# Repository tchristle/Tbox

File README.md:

# Tbox
Teensy3, esp8266, HC05, ssd1306, imu, and GPS in a kit

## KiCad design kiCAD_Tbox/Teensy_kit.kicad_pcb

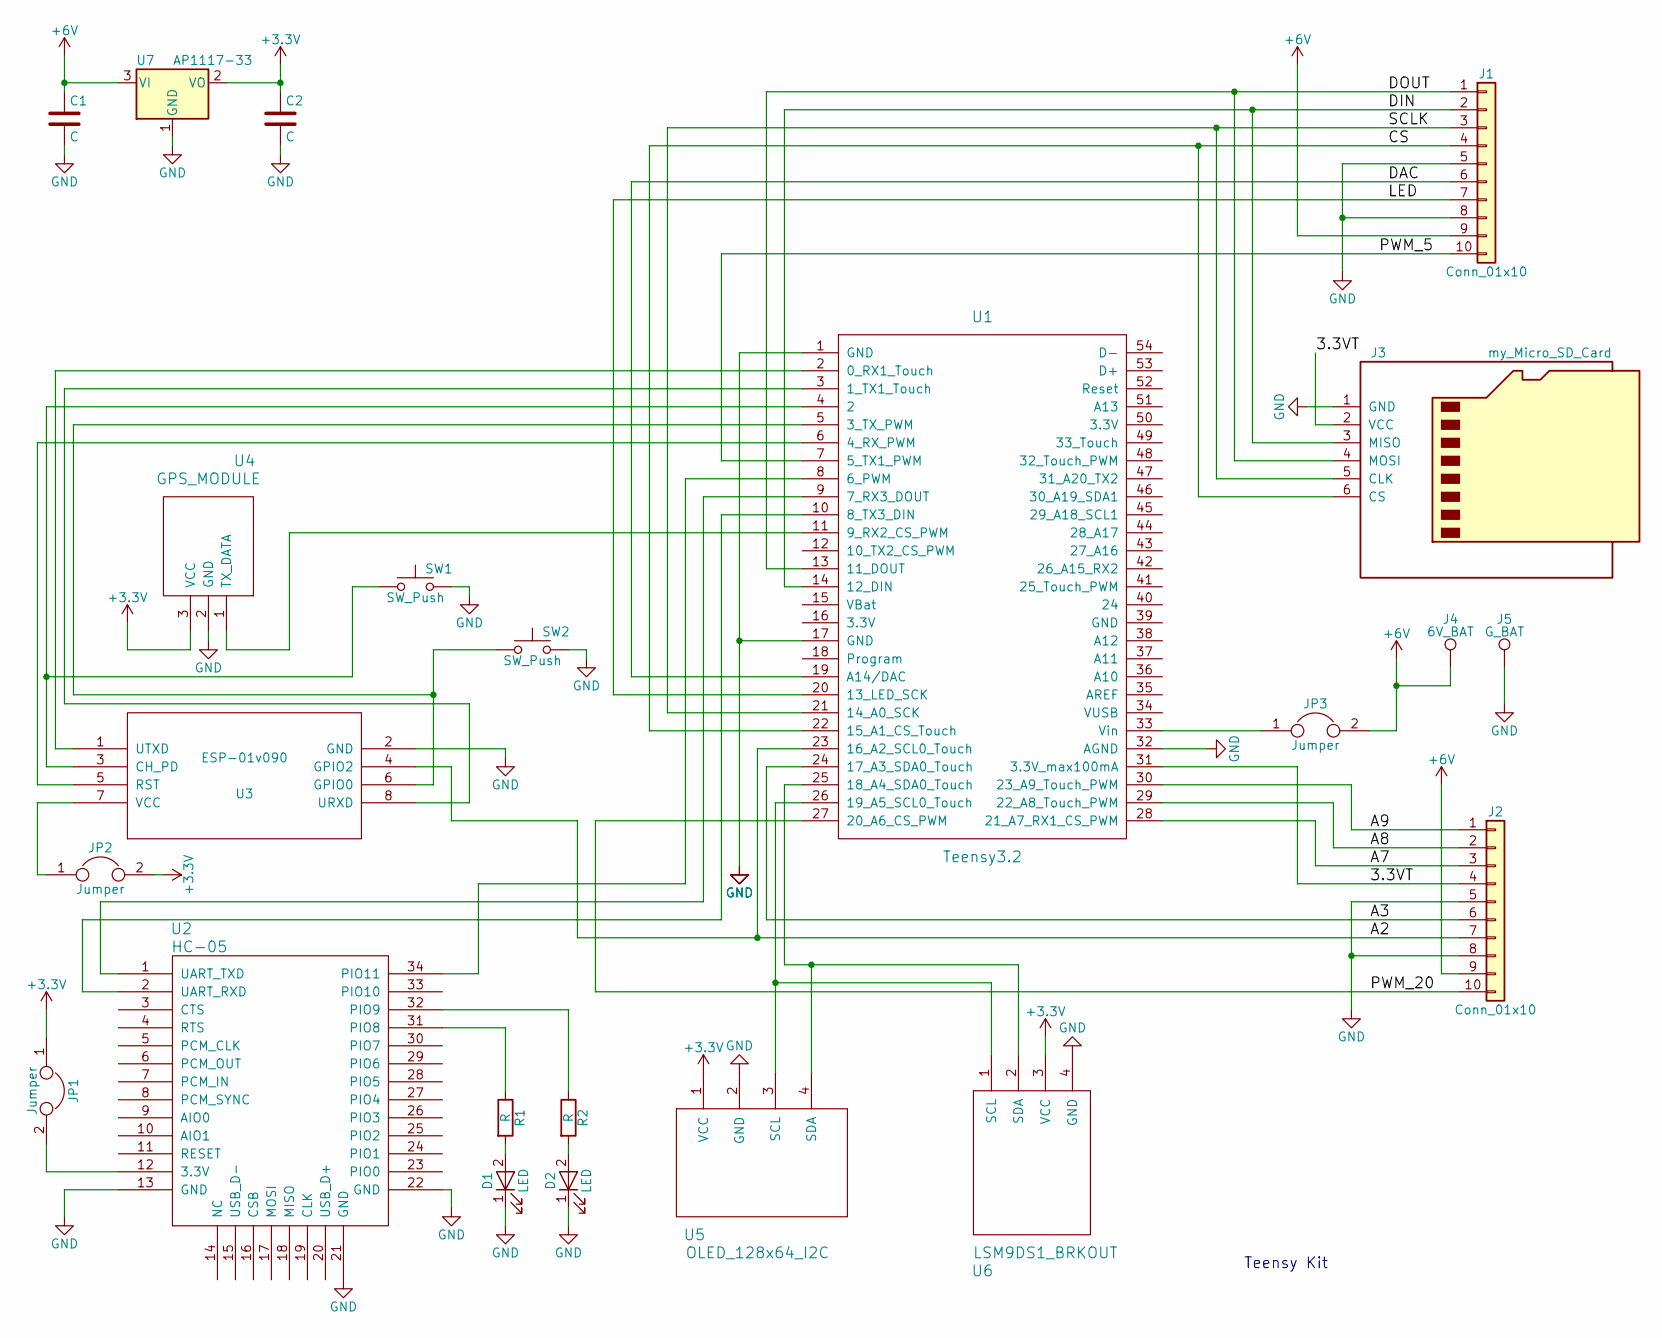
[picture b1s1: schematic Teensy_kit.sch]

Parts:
C1, C2: C; C_1812
D1, D2: LED; R_0402
J1, J2: Conn_01x10; Pin_Header_Straight_1x10_Pitch2.54mm
J3: my_Micro_SD_Card; my_microSD
J4: 6V_BAT; SolderWirePad_single_SMD_5x10mm
J5: G_BAT; SolderWirePad_single_SMD_5x10mm
JP1, JP2, JP3: Jumper; Pin_Header_Straight_1x02_Pitch2.54mm
R1, R2: R; R_0805
SW1, SW2: SW_Push; SW_SPST_B3U-1000P
U1: Teensy3.2; Teensy30_31_32_LC
U2: HC-05
U3: ESP-01v090; ESP-01
U4: GPS_MODULE; GPS
U5: OLED_128x64_I2C; OLED
U6: LSM9DS1_BRKOUT; IMU
U7: AP1117-33; SOT-223-3_TabPin2

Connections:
+3V3: C2.1, JP1.1, JP2.2, U4.3 (VCC), U5.1 (VCC), U6.3 (VCC), U7.2 (VO)
+6V: C1.1, J1.9, J2.9, J4.1, JP3.2, U7.3 (VI)
/3.3VT: J2.4, J3.2 (VCC), U1.31 (3.3V_max100mA)
/A2: J2.7, U1.23 (16_A2_SCL0_Touch), U3.4 (GPIO2)
/A3: J2.6, U1.24 (17_A3_SDA0_Touch)
/A7: J2.3, U1.28 (21_A7_RX1_CS_PWM)
/A8: J2.2, U1.29 (22_A8_Touch_PWM)
/A9: J2.1, U1.30 (23_A9_Touch_PWM)
/CS: J1.4, J3.6 (CS), U1.22 (15_A1_CS_Touch)
/DAC: J1.6, U1.19 (A14/DAC)
/DIN: J1.2, J3.3 (MISO), U1.14 (12_DIN)
/DOUT: J1.1, J3.4 (MOSI), U1.13 (11_DOUT)
/LED: J1.7, U1.20 (13_LED_SCK)
/PWM_5: J1.10, U1.7 (5_TX1_PWM)
/PWM_20: J2.10, U1.27 (20_A6_CS_PWM)
/SCLK: J1.3, J3.5 (CLK), U1.21 (14_A0_SCK)
GND: C1.2, C2.2, D1.1 (K), D2.1 (K), J1.5, J1.8, J2.5, J2.8, J3.1 (GND), J5.1, SW1.2, SW2.2, U1.1 (GND), U1.17 (GND), U1.32 (AGND), U2.13 (GND), U2.21 (GND), U2.22 (GND), U3.2 (GND), U4.2 (GND), U5.2 (GND), U6.4 (GND), U7.1 (GND)
unnamed: D1.2 (A), R1.2
unnamed: D2.2 (A), R2.2
unnamed: JP1.2, U2.12 (3.3V)
unnamed: JP2.1, U3.7 (VCC)
unnamed: JP3.1, U1.33 (Vin)
unnamed: R1.1, U2.31 (PIO8)
unnamed: R2.1, U2.32 (PIO9)
unnamed: SW1.1, U1.4 (2), U3.3 (CH_PD)
unnamed: SW2.1, U1.5 (3_TX_PWM), U3.6 (GPIO0)
unnamed: U1.2 (0_RX1_Touch), U3.1 (UTXD)
unnamed: U1.3 (1_TX1_Touch), U3.8 (URXD)
unnamed: U1.6 (4_RX_PWM), U3.5 (RST)
unnamed: U1.8 (6_PWM), U2.34 (PIO11)
unnamed: U1.9 (7_RX3_DOUT), U2.1 (UART_TXD)
unnamed: U1.10 (8_TX3_DIN), U2.2 (UART_RXD)
unnamed: U1.11 (9_RX2_CS_PWM), U4.1 (TX_DATA)
unnamed: U1.25 (18_A4_SDA0_Touch), U5.4 (SDA), U6.2 (SDA)
unnamed: U1.26 (19_A5_SCL0_Touch), U5.3 (SCL), U6.1 (SCL)

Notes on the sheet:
Teensy Kit

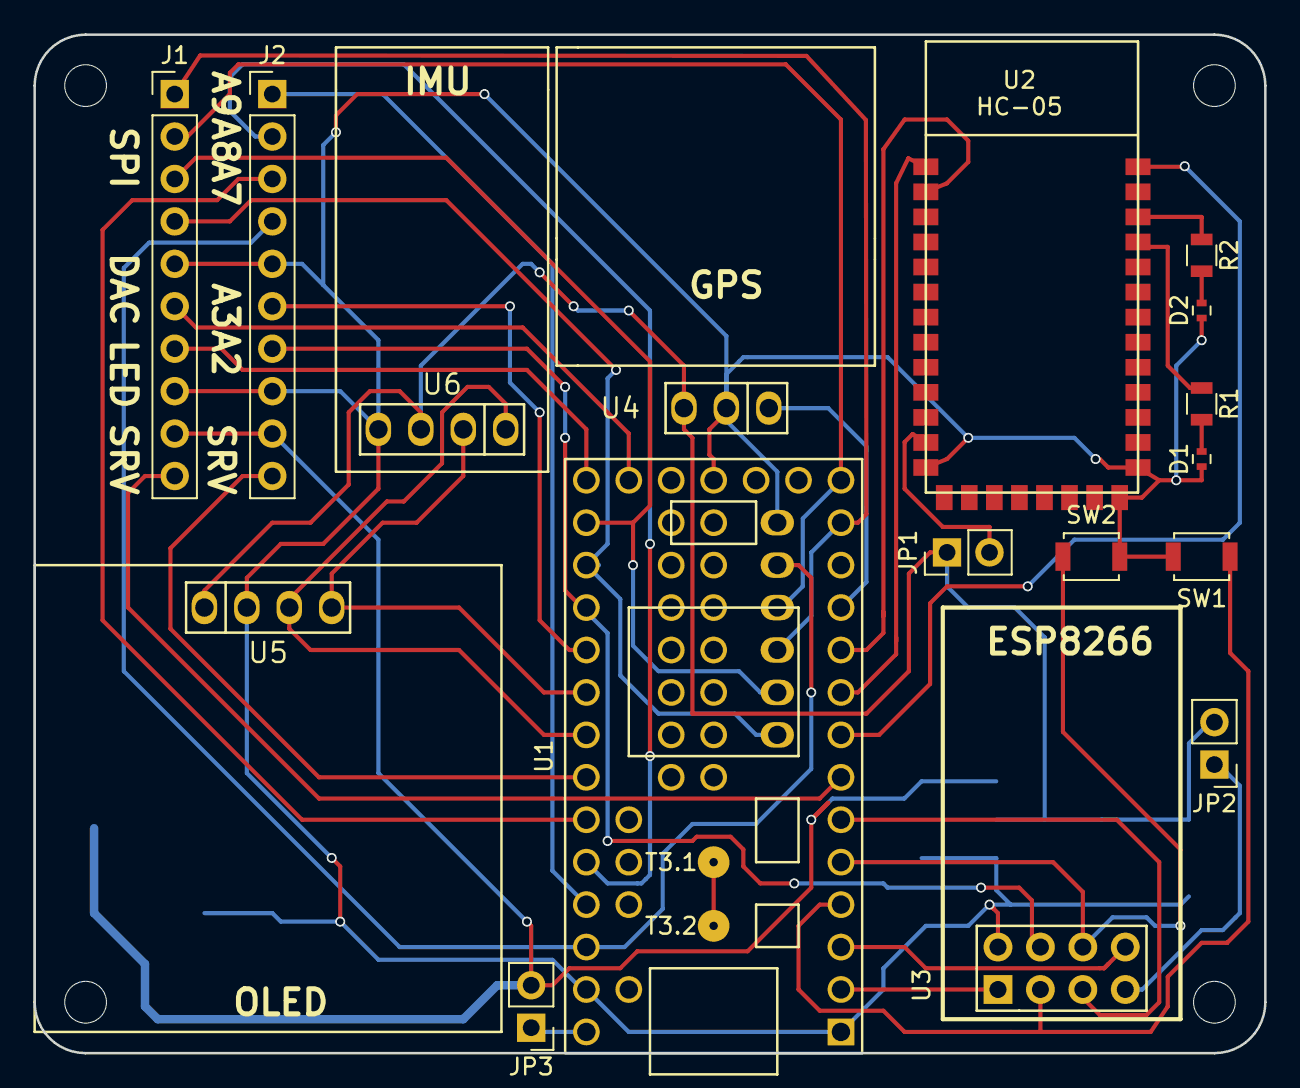
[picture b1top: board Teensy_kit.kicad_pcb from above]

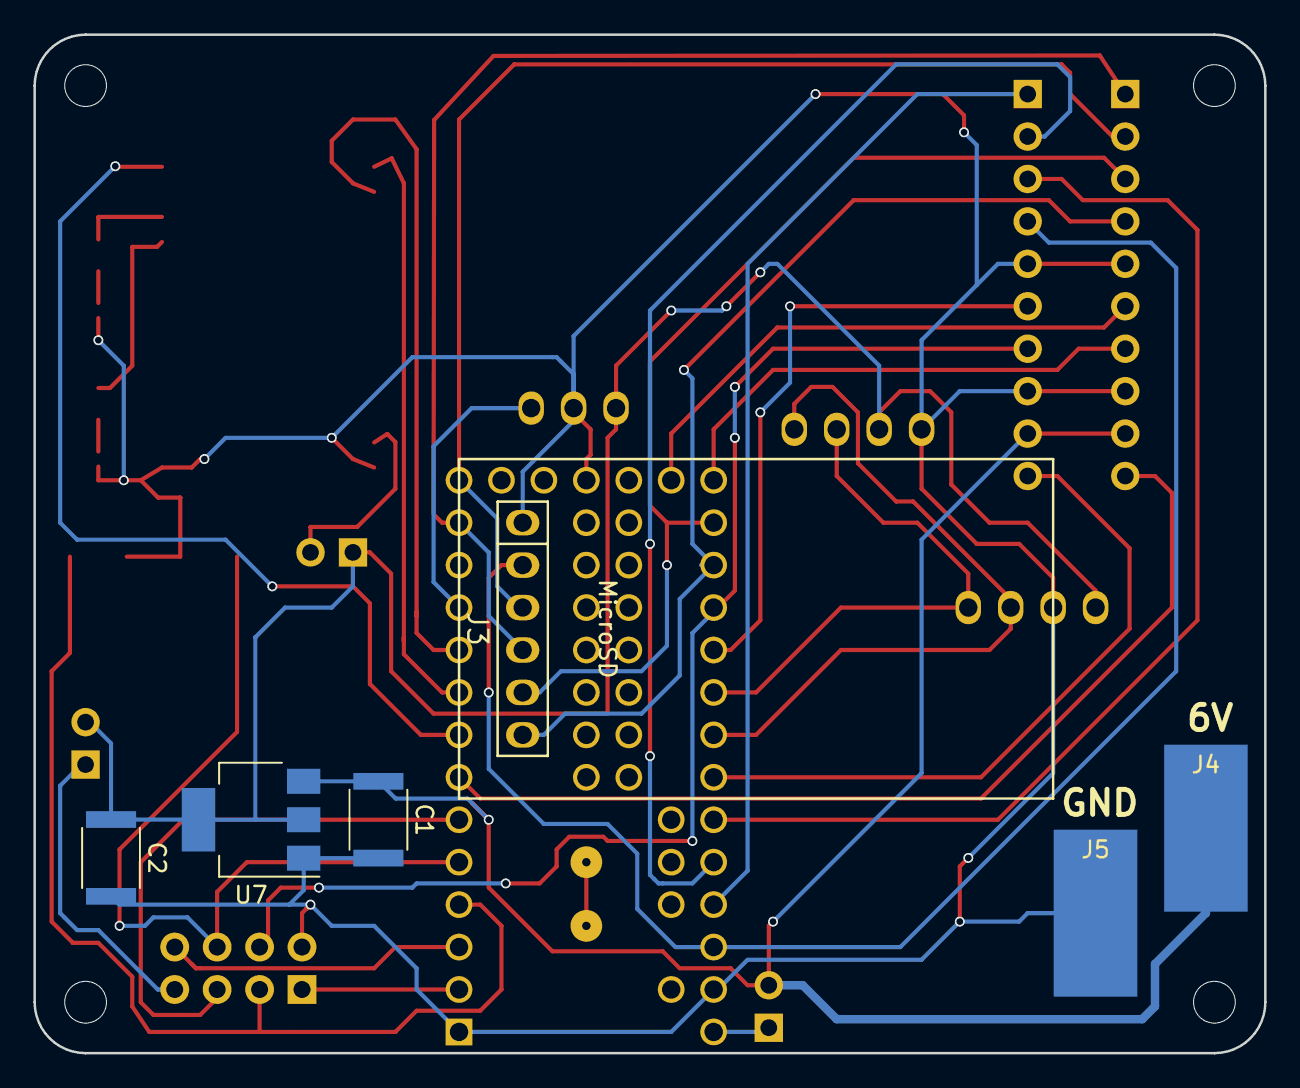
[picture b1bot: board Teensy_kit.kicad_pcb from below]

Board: 2 copper layers, 73.7 x 61.0 mm, 23 parts (6 on the bottom side), 35 nets.

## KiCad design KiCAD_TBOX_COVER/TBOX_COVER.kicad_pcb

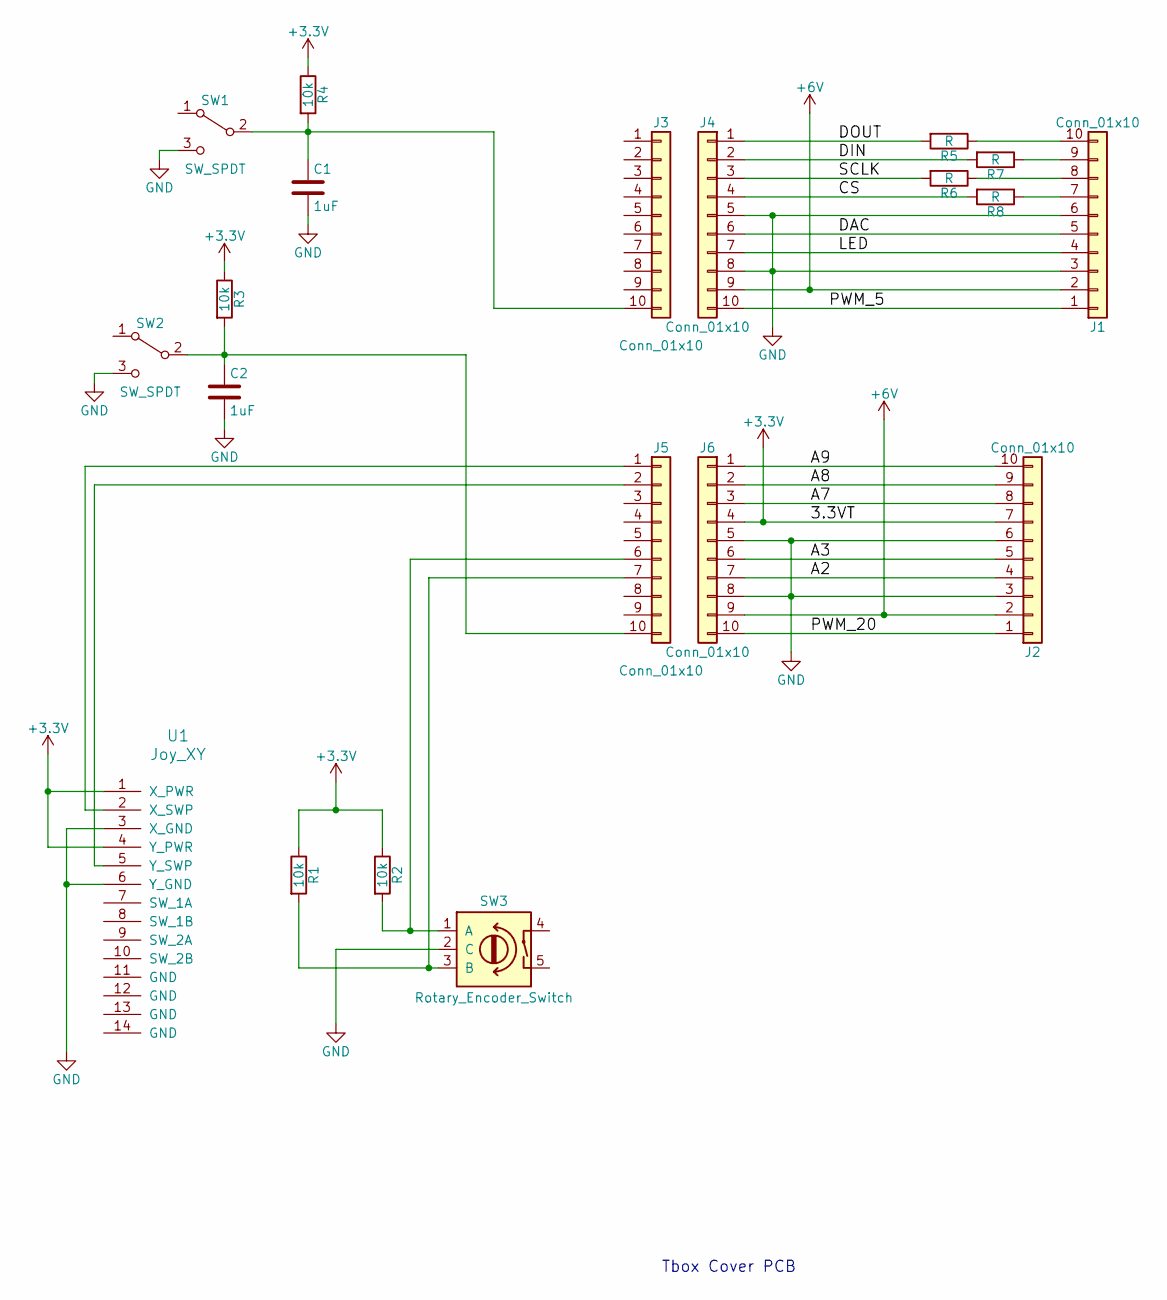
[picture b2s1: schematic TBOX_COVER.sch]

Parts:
C1, C2: 1uF; C_0805_HandSoldering
J1, J2: Conn_01x10; Socket_Strip_Straight_1x10_Pitch2.54mm
J3, J4, J5, J6: Conn_01x10; Pin_Header_Straight_1x10_Pitch2.54mm
R1, R2, R3, R4: 10k; R_0805_HandSoldering
R5, R6, R7, R8: R; R_0603_HandSoldering
SW1, SW2: SW_SPDT; Pin_Header_Straight_1x03_Pitch2.54mm
SW3: Rotary_Encoder_Switch; KSA_Tactile_SPST
U1: Joy_XY; joy_xy

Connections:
+3V3: J2.7, J6.4, R1.1, R2.1, R3.1, R4.1, U1.1 (X_PWR), U1.4 (Y_PWR)
+6V: J1.2, J2.2, J4.9, J6.9
/A2: J2.4, J6.7
/A3: J2.5, J6.6
/A7: J2.8, J6.3
/A8: J2.9, J6.2
/A9: J2.10, J6.1
/CS: J4.4, R8.2
/DAC: J1.5, J4.6
/DIN: J4.2, R7.2
/DOUT: J4.1, R5.2
/LED: J1.4, J4.7
/PWM_5: J1.1, J4.10
/PWM_20: J2.1, J6.10
/SCLK: J4.3, R6.2
GND: C1.2, C2.2, J1.3, J1.6, J2.3, J2.6, J4.5, J4.8, J6.5, J6.8, SW1.3 (C), SW2.3 (C), SW3.2 (C), U1.3 (X_GND), U1.6 (Y_GND)
unnamed: C1.1, J3.10, R4.2, SW1.2 (B)
unnamed: C2.1, J5.10, R3.2, SW2.2 (B)
unnamed: J1.7, R8.1
unnamed: J1.8, R6.1
unnamed: J1.9, R7.1
unnamed: J1.10, R5.1
unnamed: J5.1, U1.2 (X_SWP)
unnamed: J5.2, U1.5 (Y_SWP)
unnamed: J5.6, R2.2, SW3.1 (A)
unnamed: J5.7, R1.2, SW3.3 (B)

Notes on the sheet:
Tbox Cover PCB

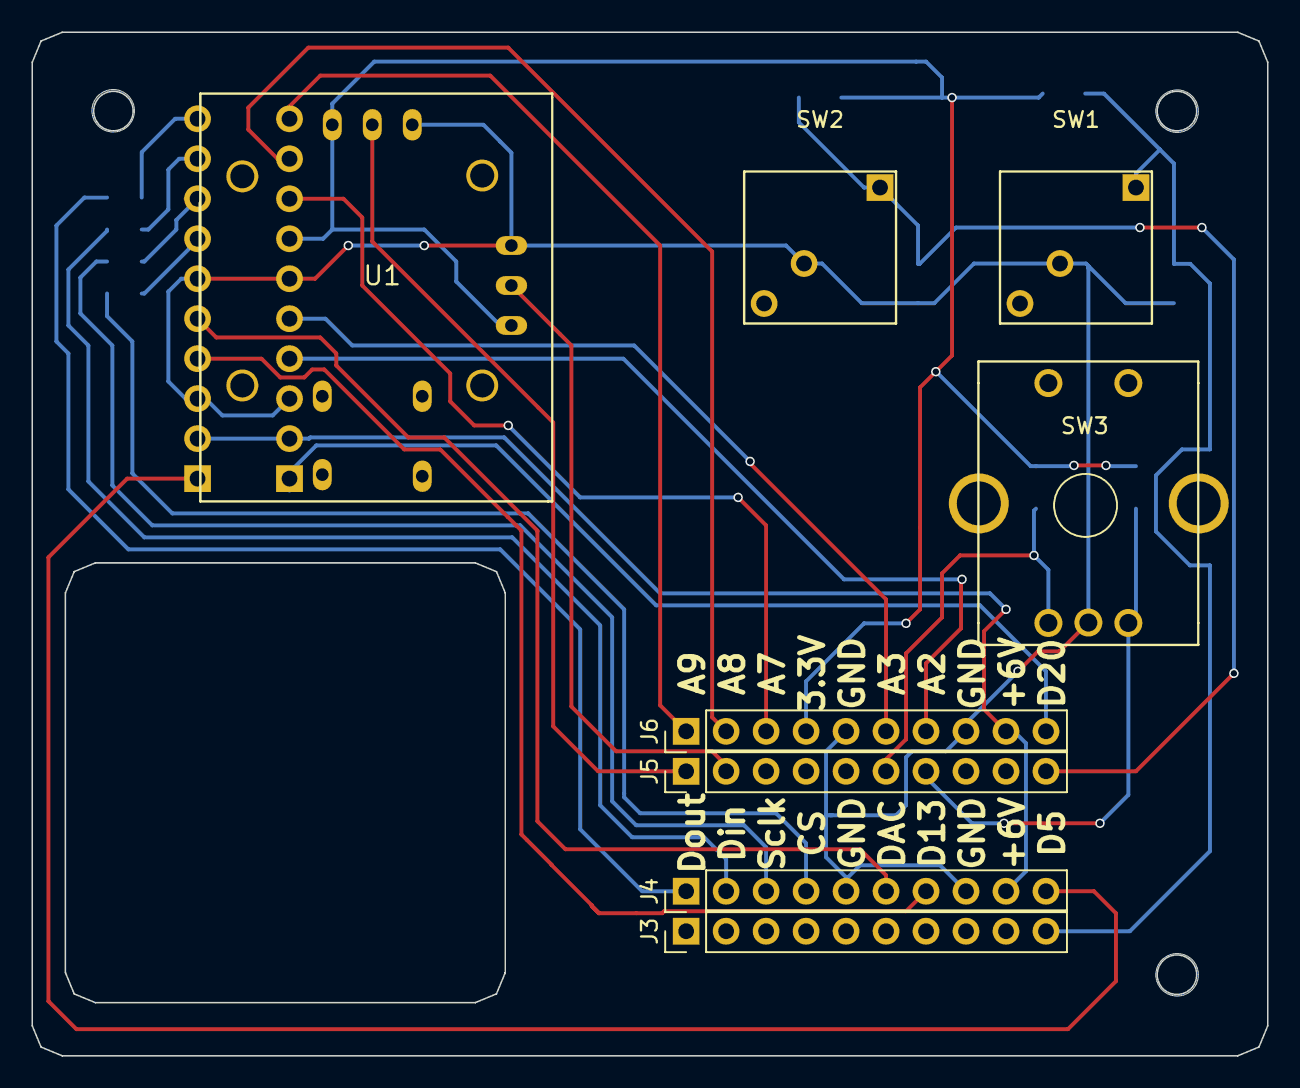
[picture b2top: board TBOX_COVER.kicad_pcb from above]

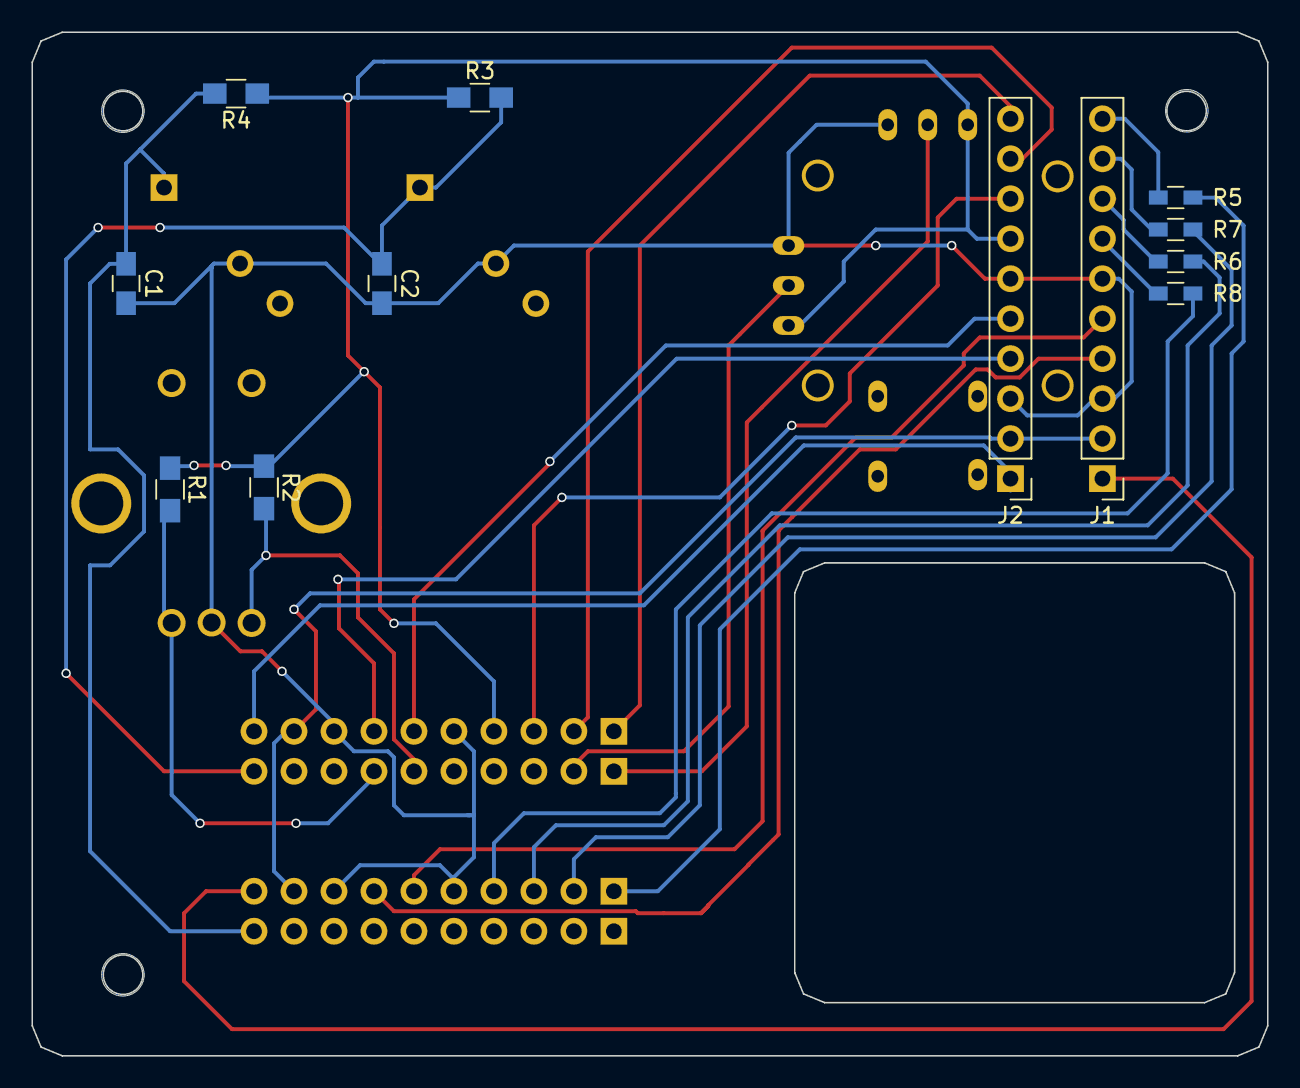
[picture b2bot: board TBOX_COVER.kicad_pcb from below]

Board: 2 copper layers, 78.5 x 65.0 mm, 20 parts (12 on the bottom side), 26 nets.

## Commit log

2019-01-17 remove old
2019-01-17 new updates
2019-01-17 new data
